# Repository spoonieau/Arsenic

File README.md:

# Smart HVAC Probe

A ESP32-C3 based probe designed for the the automatic matching of r1234yf, r134, HC-30 and R744 refrigerant pressures from current atmospheric temperature.

## Features
This Probe is designed for the the automatic matching of r1234yf, r134, HC-30 and R744 refrigerant pressures from current atmospheric temperature.

It is also equipped with a vent probe for use automotive air conditioning performance testing.

Charged and programmed over USB -C 

The probe is a fully enabled WiFi device hosting its own micro web server to to display sensor and pressure data. Any device with a WiFi connection and a web browser can connect. 

Once booted the probe will broadcast a WiFi Connection with the details below.

SSID: Smart_Hvac_Probe  
Default Password: Smart_Hvac_Probe  
Probes IP: 192.168.4.1  

Once WiFi connection is established between probe and device, a device the web browser should redirect you the the hosted probes home page. If not, type the probes IP address into a connect web browser address bar.
 
Once at the Probes homepage you can change the WiFi details and set the default units to used by the probe.  
When any setting are updated the Probe will reboot and you device will need to reconnect with the new details. 

## Screenshots
PCB_V3_EE  

FireFox Mobile  

FireFox PC  

## Used Libraries
A huge thankyou to the authors of the libraries used below.  

PaulStoffregen - OneWire  
https://github.com/PaulStoffregen/OneWire

milesburton - Arduino-Temperature-Control-Library  
https://github.com/milesburton/Arduino-Temperature-Control-Library

RadioShuttle - WS2812Led  
https://github.com/RadioShuttle/WS2812Led

hideakitai - MAX17048  
https://github.com/hideakitai/MAX17048

malokhvii-eduard - arduino-bme280  
https://github.com/malokhvii-eduard/arduino-bme280

me-no-dev - ESPAsyncWebServer  
https://github.com/me-no-dev/ESPAsyncWebServer

me-no-dev - AsyncTCP  
https://github.com/me-no-dev/AsyncTCP

arduino-libraries   
https://github.com/arduino-libraries

espressif - arduino-esp32  
https://github.com/espressif/arduino-esp32

## License

Libraries that are used carry their own Licenses.  
Project is released under GPL3

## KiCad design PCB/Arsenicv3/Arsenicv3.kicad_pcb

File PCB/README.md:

KiCad PCB design files for Arsenic Smart HAVC Probe   
Current working version V3

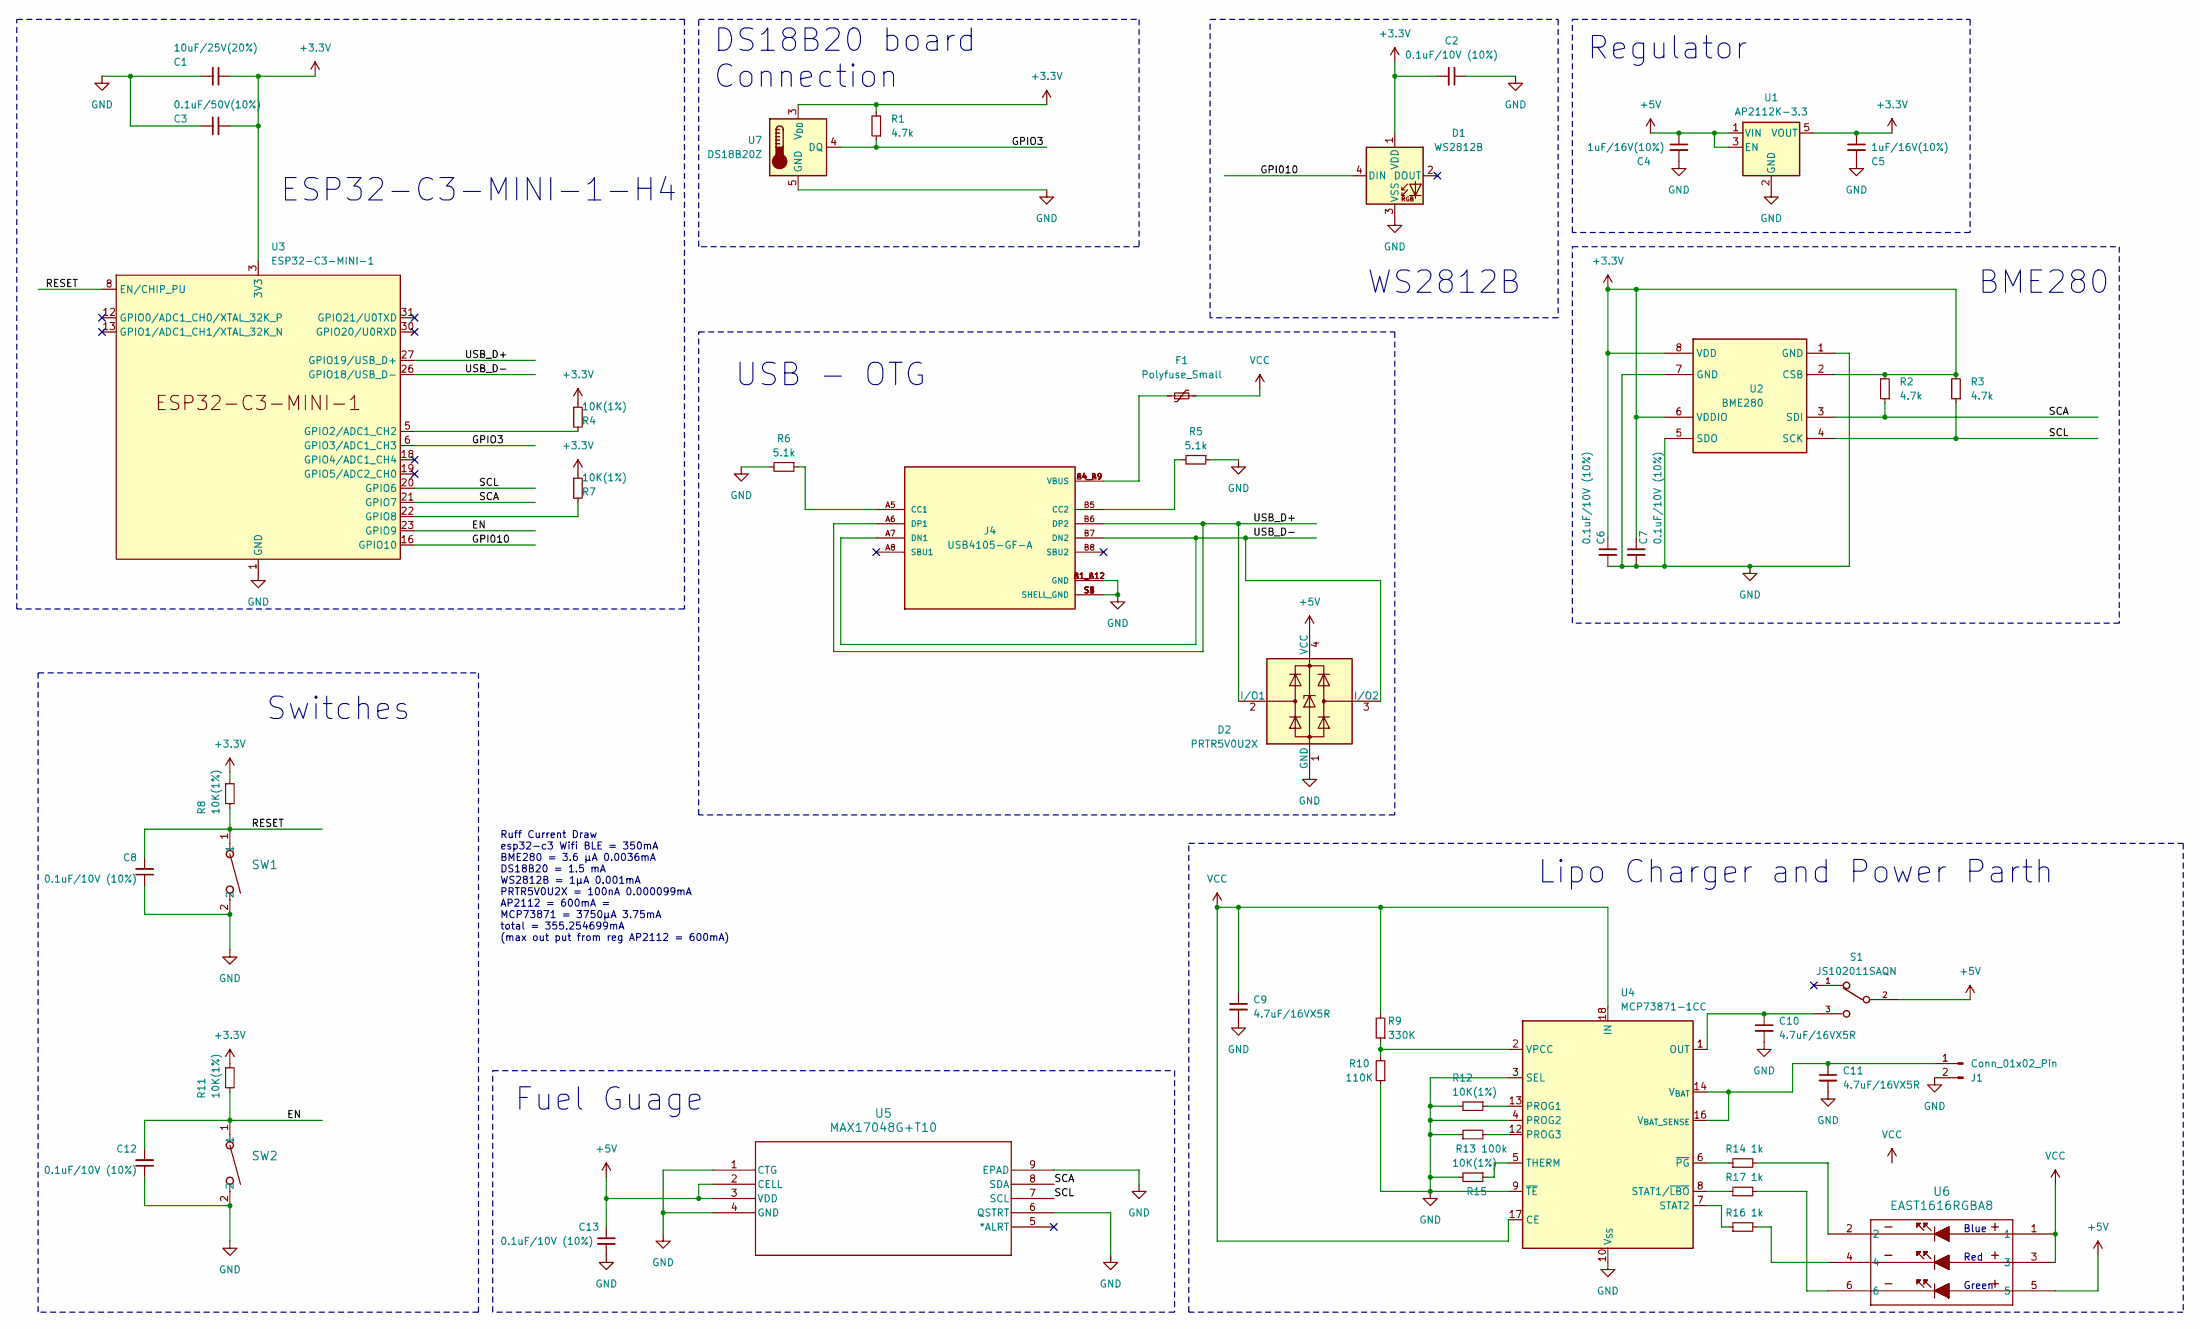
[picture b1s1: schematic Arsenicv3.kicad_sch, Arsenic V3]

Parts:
C1: 10uF/25V(20%); C_0603_1608Metric_Pad1.08x0.95mm_HandSolder; DigiKeyPN 1276-1869-1-ND
C2, C6, C7, C8, C12, C13: 0.1uF/10V (10%); C_0402_1005Metric_Pad0.74x0.62mm_HandSolder; DigiKeyPN 1276-1022-1-ND
C3: 0.1uF/50V(10%); C_0402_1005Metric_Pad0.74x0.62mm_HandSolder; DigiKeyPN 490-GRM155R61H104ME14DCT-ND
C4, C5: 1uF/16V(10%); C_0402_1005Metric_Pad0.74x0.62mm_HandSolder; DigiKeyPN 1276-1067-1-ND
C9, C10, C11: 4.7uF/16VX5R; C_0402_1005Metric_Pad0.74x0.62mm_HandSolder; DigiKeyPN 478-CM05X5R475M16AHCT-ND
D1: WS2812B; LED_WS2812B_PLCC4_5.0x5.0mm_P3.2mm; DigiKeyPN 1568-COM-16347CT-ND
D2: PRTR5V0U2X; SOT-143; DigiKeyPN 1727-3884-1-ND
F1: Polyfuse_Small; Fuse_0805_2012Metric_Pad1.15x1.40mm_HandSolder; DigiKeyPN 13-SMD0805B075TFCT-ND
J1: Conn_01x02_Pin; PinHeader_1x02_P2.00mm_Vertical
J4: USB4105-GF-A; GCT_USB4105-GF-A; DigiKeyPN 2073-USB4105-GF-ACT-ND
R1, R2, R3: 4.7k; R_0402_1005Metric_Pad0.72x0.64mm_HandSolder; DigiKeyPN 311-4.7KLRCT-ND
R4, R7, R8, R11, R12, R15: 10K(1%); C_0402_1005Metric_Pad0.74x0.62mm_HandSolder; DigiKeyPN 311-10.0KLRCT-ND
R5, R6: 5.1k; R_0402_1005Metric_Pad0.72x0.64mm_HandSolder; DigiKeyPN 13-RC0402FR-135K1LCT-ND
R9: 330K; R_0402_1005Metric_Pad0.72x0.64mm_HandSolder; DigiKeyPN 1292-WR04X3303FTLCT-ND
R10: 110K; R_0402_1005Metric_Pad0.72x0.64mm_HandSolder; DigiKeyPN CR0402-FX-1103GLFCT-ND
R13: 100k; R_0402_1005Metric_Pad0.72x0.64mm_HandSolder; DigiKeyPN 311-100KLRCT-ND
R14, R16, R17: 1k; R_0402_1005Metric_Pad0.72x0.64mm_HandSolder; DigiKeyPN 311-1.00KLRCT-ND
S1: JS102011SAQN; SW_JS102011SAQN; DigiKeyPN 401-1999-1-ND
SW1, SW2: KXT331LHS; KXT3_CNK; DigiKeyPN CKN10779CT-ND
U1: AP2112K-3.3; SOT-23-5; DigiKeyPN AP2112K-3.3TRG1DICT-ND
U2: BME280; Bosch_LGA-8_2.5x2.5mm_P0.65mm_ClockwisePinNumbering; DigiKeyPN 828-1063-1-ND
U3: ESP32-C3-MINI-1; DigiKeyPN 1965-ESP32-C3-MINI-1-H4CT-ND
U4: MCP73871-1CC; QFN-20-1EP_4x4mm_P0.5mm_EP2.5x2.5mm; DigiKeyPN MCP73871-1CCI/ML-ND
U5: MAX17048G+T10; 21-0168E_T822-3_MXM; DigiKeyPN MAX17048G+T10CT-ND
U6: EAST1616RGBA8; LED_EAST1616RGBA8; DigiKeyPN 1080-EAST1616RGBA8CT-ND
U7: DS18B20Z; SOIC-8_3.9x4.9mm_P1.27mm; DigiKeyPN 4518-DS18B20ZCT-ND

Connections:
+3.3V: C1.1, C2.2, C3.1, C5.1, C6.1, C7.1, D1.1 (VDD), R1.2, R2.2, R3.2, R4.1, R7.1, R8.1, R11.1, U1.5 (VOUT), U2.2 (CSB), U2.6 (VDDIO), U2.8 (VDD), U3.3 (3V3), U7.3 (V_{DD})
+5V: C4.1, C13.1, D2.4 (VCC), S1.2, U1.1 (VIN), U1.3 (EN), U5.2 (CELL), U5.3 (VDD), U6.5
/EN: C12.2, R11.2, SW2.1, U3.23 (GPIO9)
/GPI010: D1.4 (DIN), U3.16 (GPIO10)
/GPIO3: R1.1, U3.6 (GPIO3/ADC1_CH3), U7.4 (DQ)
/RESET: C8.2, R8.2, SW1.1, U3.8 (EN/CHIP_PU)
/SCA: R2.1, U2.3 (SDI), U3.21 (GPIO7), U5.8 (SDA)
/SCL: R3.1, U2.4 (SCK), U3.20 (GPIO6), U5.7 (SCL)
/USB_D+: D2.2 (I/O1), J4.A6 (DP1), J4.B6 (DP2), U3.27 (GPIO19/USB_D+)
/USB_D-: D2.3 (I/O2), J4.A7 (DN1), J4.B7 (DN2), U3.26 (GPIO18/USB_D-)
GND: C1.2, C2.1, C3.2, C4.2, C5.2, C6.2, C7.2, C8.1, C9.2, C10.2, C11.2, C12.1, C13.2, D1.3 (VSS), D2.1 (GND), J1.2, J4.A1_B12 (GND), J4.B1_A12 (GND), J4.S1 (SHELL_GND), J4.S2 (SHELL_GND), J4.S3 (SHELL_GND), J4.S4 (SHELL_GND), R5.1, R6.2, R10.1, R12.2, R13.1, R15.2, SW1.2, SW2.2, U1.2 (GND), U2.1 (GND), U2.5 (SDO), U2.7 (GND), U3.1 (GND), U3.2 (GND), U3.11 (GND), U3.14 (GND), U3.36 (GND), U3.37 (GND), U3.38 (GND), U3.39 (GND), U3.40 (GND), U3.41 (GND), U3.42 (GND), U3.43 (GND), U3.44 (GND), U3.45 (GND), U3.46 (GND), U3.47 (GND), U3.48 (GND), U3.49 (GND), U3.50 (GND), U3.51 (GND), U3.52 (GND), U3.53 (GND), U4.3 (SEL), U4.4 (PROG2), U4.9 (~TE), U4.10 (V_{SS}), U4.11 (V_{SS}), U4.21 (V_{SS}), U5.1 (CTG), U5.4 (GND), U5.6 (QSTRT), U5.9 (EPAD), U7.5 (GND)
unnamed: C10.1, S1.3, U4.1 (OUT), U4.20 (OUT)
unnamed: F1.1, J4.A4_B9 (VBUS), J4.B4_A9 (VBUS)
unnamed: C11.1, J1.1, U4.14 (V_{BAT}), U4.15 (V_{BAT}), U4.16 (V_{BAT_SENSE})
unnamed: J4.A5 (CC1), R6.1
unnamed: J4.B5 (CC2), R5.2
unnamed: R14.2, U6.2
unnamed: R16.2, U6.4
unnamed: R17.2, U6.6
unnamed: R4.2, U3.5 (GPIO2/ADC1_CH2)
unnamed: R7.2, U3.22 (GPIO8)
unnamed: R12.1, U4.13 (PROG1)
unnamed: R13.2, U4.12 (PROG3)
unnamed: R17.1, U4.8 (STAT1/~LBO)
unnamed: R16.1, U4.7 (STAT2)
unnamed: R15.1, U4.5 (THERM)
unnamed: R9.1, R10.2, U4.2 (VPCC)
unnamed: R14.1, U4.6 (~PG)
VCC: C9.1, F1.2, R9.2, U4.17 (CE), U4.18 (IN), U4.19 (IN), U6.1, U6.3

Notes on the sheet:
WS2812B
Regulator
Fuel Guage
Lipo Charger and Power Parth
Green
USB - OTG
ESP32-C3-MINI-1-H4
BME280
Switches
Red
Blue
Ruff Current Draw esp32-c3 Wifi BLE = 350mA BME280 = 3.6 μA 0.0036mA DS18B20 = 1.5 mA WS2812B = 1μA 0.001mA PRTR5V0U2X = 100nA 0.000099mA AP2112 = 600mA = MCP73871 = 3750μA 3.75mA total = 355.254699mA (max out put from reg AP2112 = 600mA)
DS18B20 board Connection

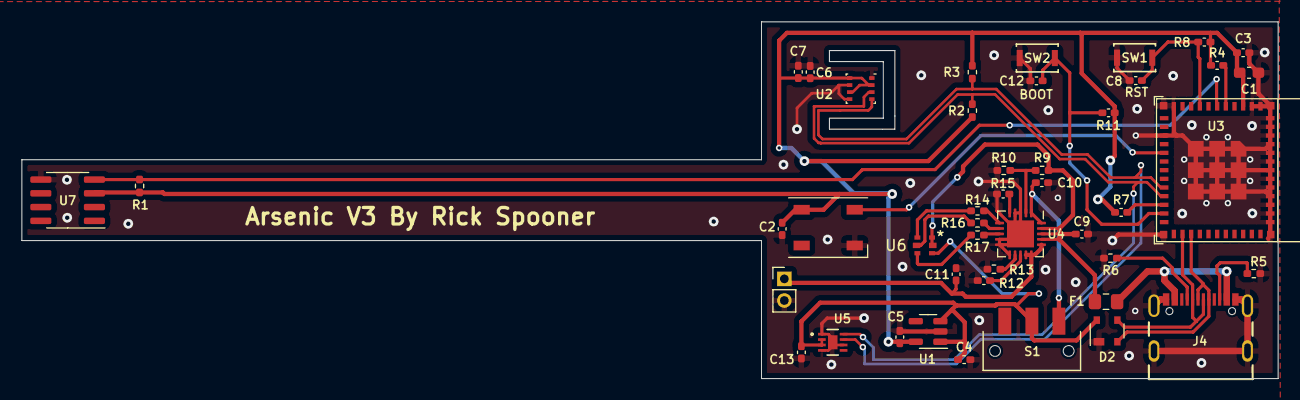
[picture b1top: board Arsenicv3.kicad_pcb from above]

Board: 2 copper layers, 116.0 x 33.0 mm, 45 parts (0 on the bottom side), 29 nets.

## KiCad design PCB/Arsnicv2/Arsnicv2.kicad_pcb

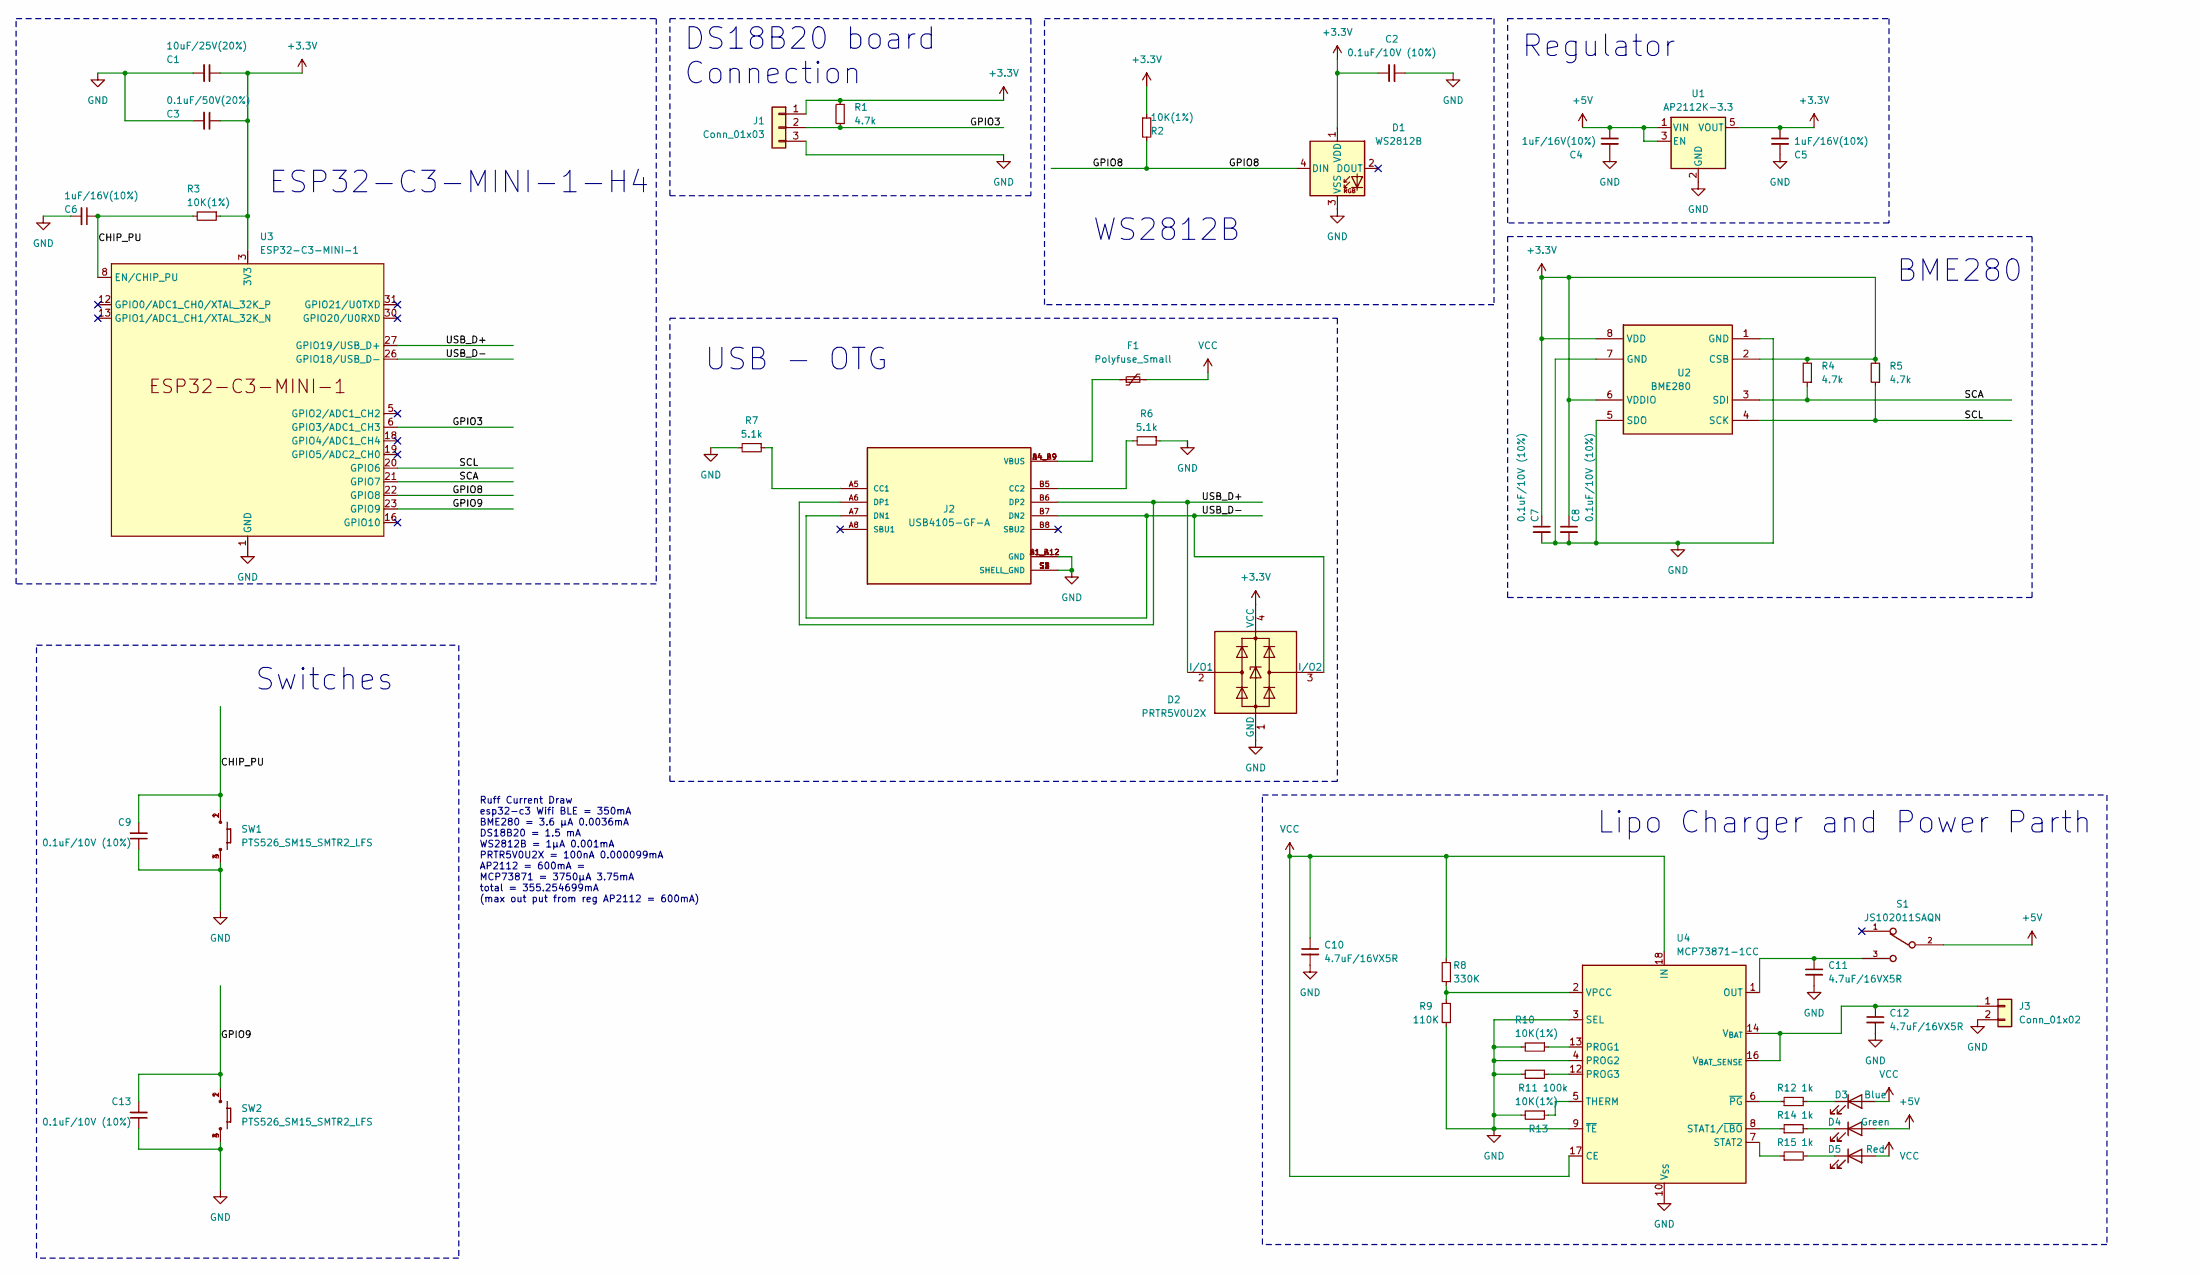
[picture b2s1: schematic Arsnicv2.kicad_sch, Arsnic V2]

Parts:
C1: 10uF/25V(20%); C_0603_1608Metric_Pad1.08x0.95mm_HandSolder; DigiKeyPN 1276-1869-1-ND
C2, C7, C8, C9, C13: 0.1uF/10V (10%); C_0402_1005Metric_Pad0.74x0.62mm_HandSolder; DigiKeyPN 1276-1022-1-ND
C3: 0.1uF/50V(20%); C_0402_1005Metric_Pad0.74x0.62mm_HandSolder; DigiKeyPN 490-GRM155R61H104ME14DCT-ND
C4, C5, C6: 1uF/16V(10%); C_0402_1005Metric_Pad0.74x0.62mm_HandSolder; DigiKeyPN 1276-1067-1-ND
C10, C11, C12: 4.7uF/16VX5R; C_0402_1005Metric_Pad0.74x0.62mm_HandSolder; DigiKeyPN 478-CM05X5R475M16AHCT-ND
D1: WS2812B; LED_WS2812B_PLCC4_5.0x5.0mm_P3.2mm; DigiKeyPN 1568-COM-16347CT-ND
D2: PRTR5V0U2X; SOT-143; DigiKeyPN 1727-3884-1-ND
D3: Blue; LED_0201_0603Metric_Pad0.64x0.40mm_HandSolder; DigiKeyPN 1830-1068-1-ND
D4: Green; LED_0201_0603Metric_Pad0.64x0.40mm_HandSolder; DigiKeyPN 1830-1069-1-ND
D5: Red; LED_0201_0603Metric_Pad0.64x0.40mm_HandSolder; DigiKeyPN 1830-1072-1-ND
F1: Polyfuse_Small; Fuse_0805_2012Metric_Pad1.15x1.40mm_HandSolder; DigiKeyPN 13-SMD0805B075TFCT-ND
J1: Conn_01x03; JST_PH_S3B-PH-K_1x03_P2.00mm_Horizontal; DigiKeyPN S3B-PH-K-S-GW-ND
J2: USB4105-GF-A; GCT_USB4105-GF-A; DigiKeyPN 2073-USB4105-GF-ACT-ND
J3: Conn_01x02; JST_PH_S2B-PH-K_1x02_P2.00mm_Horizontal; DigiKeyPN 455-1719-ND
R1, R4, R5: 4.7k; R_0402_1005Metric_Pad0.72x0.64mm_HandSolder; DigiKeyPN 311-4.7KLRCT-ND
R2, R3, R10, R13: 10K(1%); C_0402_1005Metric_Pad0.74x0.62mm_HandSolder; DigiKeyPN 311-10.0KLRCT-ND
R6, R7: 5.1k; R_0402_1005Metric_Pad0.72x0.64mm_HandSolder; DigiKeyPN 13-RC0402FR-135K1LCT-ND
R8: 330K; R_0402_1005Metric_Pad0.72x0.64mm_HandSolder; DigiKeyPN 1292-WR04X3303FTLCT-ND
R9: 110K; R_0402_1005Metric_Pad0.72x0.64mm_HandSolder; DigiKeyPN CR0402-FX-1103GLFCT-ND
R11: 100k; R_0402_1005Metric_Pad0.72x0.64mm_HandSolder; DigiKeyPN 311-100KLRCT-ND
R12, R14, R15: 1k; R_0402_1005Metric_Pad0.72x0.64mm_HandSolder; DigiKeyPN 311-1.00KLRCT-ND
S1: JS102011SAQN; SW_JS102011SAQN; DigiKeyPN 401-1999-1-ND
SW1, SW2: PTS526_SM15_SMTR2_LFS; PTS526SM15SMTR2LFS; DigiKeyPN CKN12220-1-ND
U1: AP2112K-3.3; SOT-23-5; DigiKeyPN AP2112K-3.3TRG1DICT-ND
U2: BME280; Bosch_LGA-8_2.5x2.5mm_P0.65mm_ClockwisePinNumbering; DigiKeyPN 828-1063-1-ND
U3: ESP32-C3-MINI-1; ESP32-C3-MINI-1_HandSoldering; DigiKeyPN 1965-ESP32-C3-MINI-1-H4CT-ND
U4: MCP73871-1CC; QFN-20-1EP_4x4mm_P0.5mm_EP2.5x2.5mm; DigiKeyPN MCP73871-1CCI/ML-ND

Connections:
+3.3V: C1.1, C2.2, C3.1, C5.1, C7.1, C8.1, D1.1 (VDD), D2.4 (VCC), J1.1, R1.2, R2.1, R3.1, R4.2, R5.2, U1.5 (VOUT), U2.2 (CSB), U2.6 (VDDIO), U2.8 (VDD), U3.3 (3V3)
+5V: C4.1, D4.2 (A), S1.2, U1.1 (VIN), U1.3 (EN)
/CHIP_PU: C6.1, C9.2, R3.2, SW1.1, SW1.2, U3.8 (EN/CHIP_PU)
/GPIO3: J1.2, R1.1, U3.6 (GPIO3/ADC1_CH3)
/GPIO8: D1.4 (DIN), R2.2, U3.22 (GPIO8)
/GPIO9: C13.2, SW2.1, SW2.2, U3.23 (GPIO9)
/SCA: R4.1, U2.3 (SDI), U3.21 (GPIO7)
/SCL: R5.1, U2.4 (SCK), U3.20 (GPIO6)
/USB_D+: D2.2 (I/O1), J2.A6 (DP1), J2.B6 (DP2), U3.27 (GPIO19/USB_D+)
/USB_D-: D2.3 (I/O2), J2.A7 (DN1), J2.B7 (DN2), U3.26 (GPIO18/USB_D-)
GND: C1.2, C2.1, C3.2, C4.2, C5.2, C6.2, C7.2, C8.2, C9.1, C10.2, C11.2, C12.2, C13.1, D1.3 (VSS), D2.1 (GND), J1.3, J2.A1_B12 (GND), J2.B1_A12 (GND), J2.S1 (SHELL_GND), J2.S2 (SHELL_GND), J2.S3 (SHELL_GND), J2.S4 (SHELL_GND), J3.2, R6.1, R7.2, R9.1, R10.2, R11.1, R13.2, SW1.3, SW1.4, SW2.3, SW2.4, U1.2 (GND), U2.1 (GND), U2.5 (SDO), U2.7 (GND), U3.1 (GND), U3.2 (GND), U3.11 (GND), U3.14 (GND), U3.36 (GND), U3.37 (GND), U3.38 (GND), U3.39 (GND), U3.40 (GND), U3.41 (GND), U3.42 (GND), U3.43 (GND), U3.44 (GND), U3.45 (GND), U3.46 (GND), U3.47 (GND), U3.48 (GND), U3.49 (GND), U3.50 (GND), U3.51 (GND), U3.52 (GND), U3.53 (GND), U4.3 (SEL), U4.4 (PROG2), U4.9 (~TE), U4.10 (V_{SS}), U4.11 (V_{SS}), U4.21 (V_{SS})
unnamed: C11.1, S1.3, U4.1 (OUT), U4.20 (OUT)
unnamed: D3.1 (K), R12.2
unnamed: D4.1 (K), R14.2
unnamed: D5.1 (K), R15.2
unnamed: F1.1, J2.A4_B9 (VBUS), J2.B4_A9 (VBUS)
unnamed: J2.A5 (CC1), R7.1
unnamed: J2.B5 (CC2), R6.2
unnamed: C12.1, J3.1, U4.14 (V_{BAT}), U4.15 (V_{BAT}), U4.16 (V_{BAT_SENSE})
unnamed: R10.1, U4.13 (PROG1)
unnamed: R11.2, U4.12 (PROG3)
unnamed: R14.1, U4.8 (STAT1/~LBO)
unnamed: R15.1, U4.7 (STAT2)
unnamed: R13.1, U4.5 (THERM)
unnamed: R8.1, R9.2, U4.2 (VPCC)
unnamed: R12.1, U4.6 (~PG)
VCC: C10.1, D3.2 (A), D5.2 (A), F1.2, R8.2, U4.17 (CE), U4.18 (IN), U4.19 (IN)

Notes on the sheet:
WS2812B
Regulator
Lipo Charger and Power Parth
USB - OTG
ESP32-C3-MINI-1-H4
BME280
Switches
Ruff Current Draw esp32-c3 Wifi BLE = 350mA BME280 = 3.6 μA 0.0036mA DS18B20 = 1.5 mA WS2812B = 1μA 0.001mA PRTR5V0U2X = 100nA 0.000099mA AP2112 = 600mA = MCP73871 = 3750μA 3.75mA total = 355.254699mA (max out put from reg AP2112 = 600mA)
DS18B20 board Connection

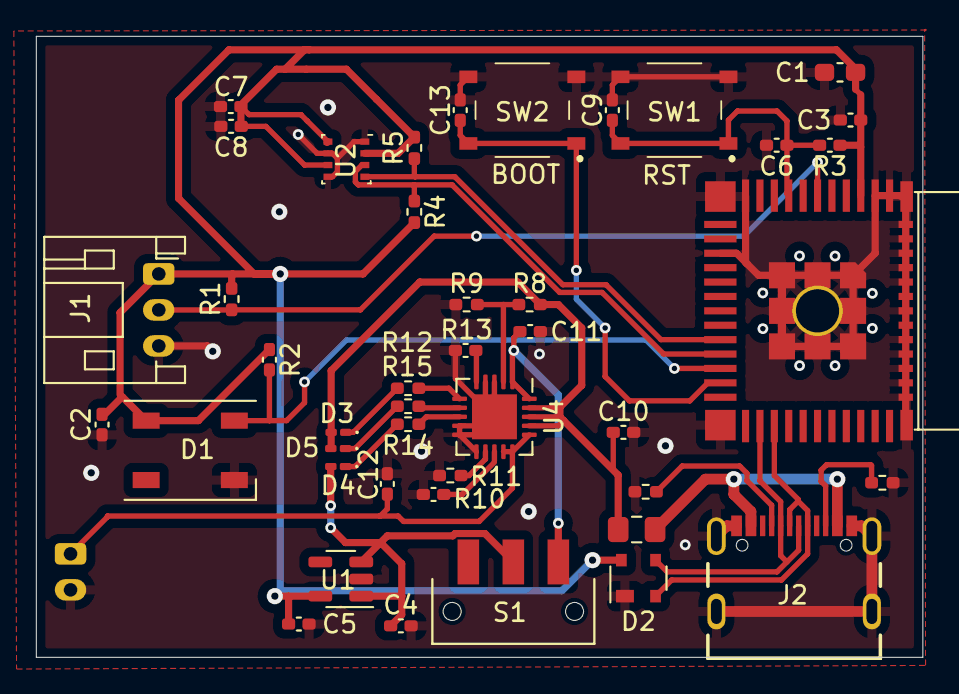
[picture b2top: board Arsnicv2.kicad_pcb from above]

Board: 2 copper layers, 49.3 x 34.5 mm, 44 parts (1 on the bottom side), 27 nets.

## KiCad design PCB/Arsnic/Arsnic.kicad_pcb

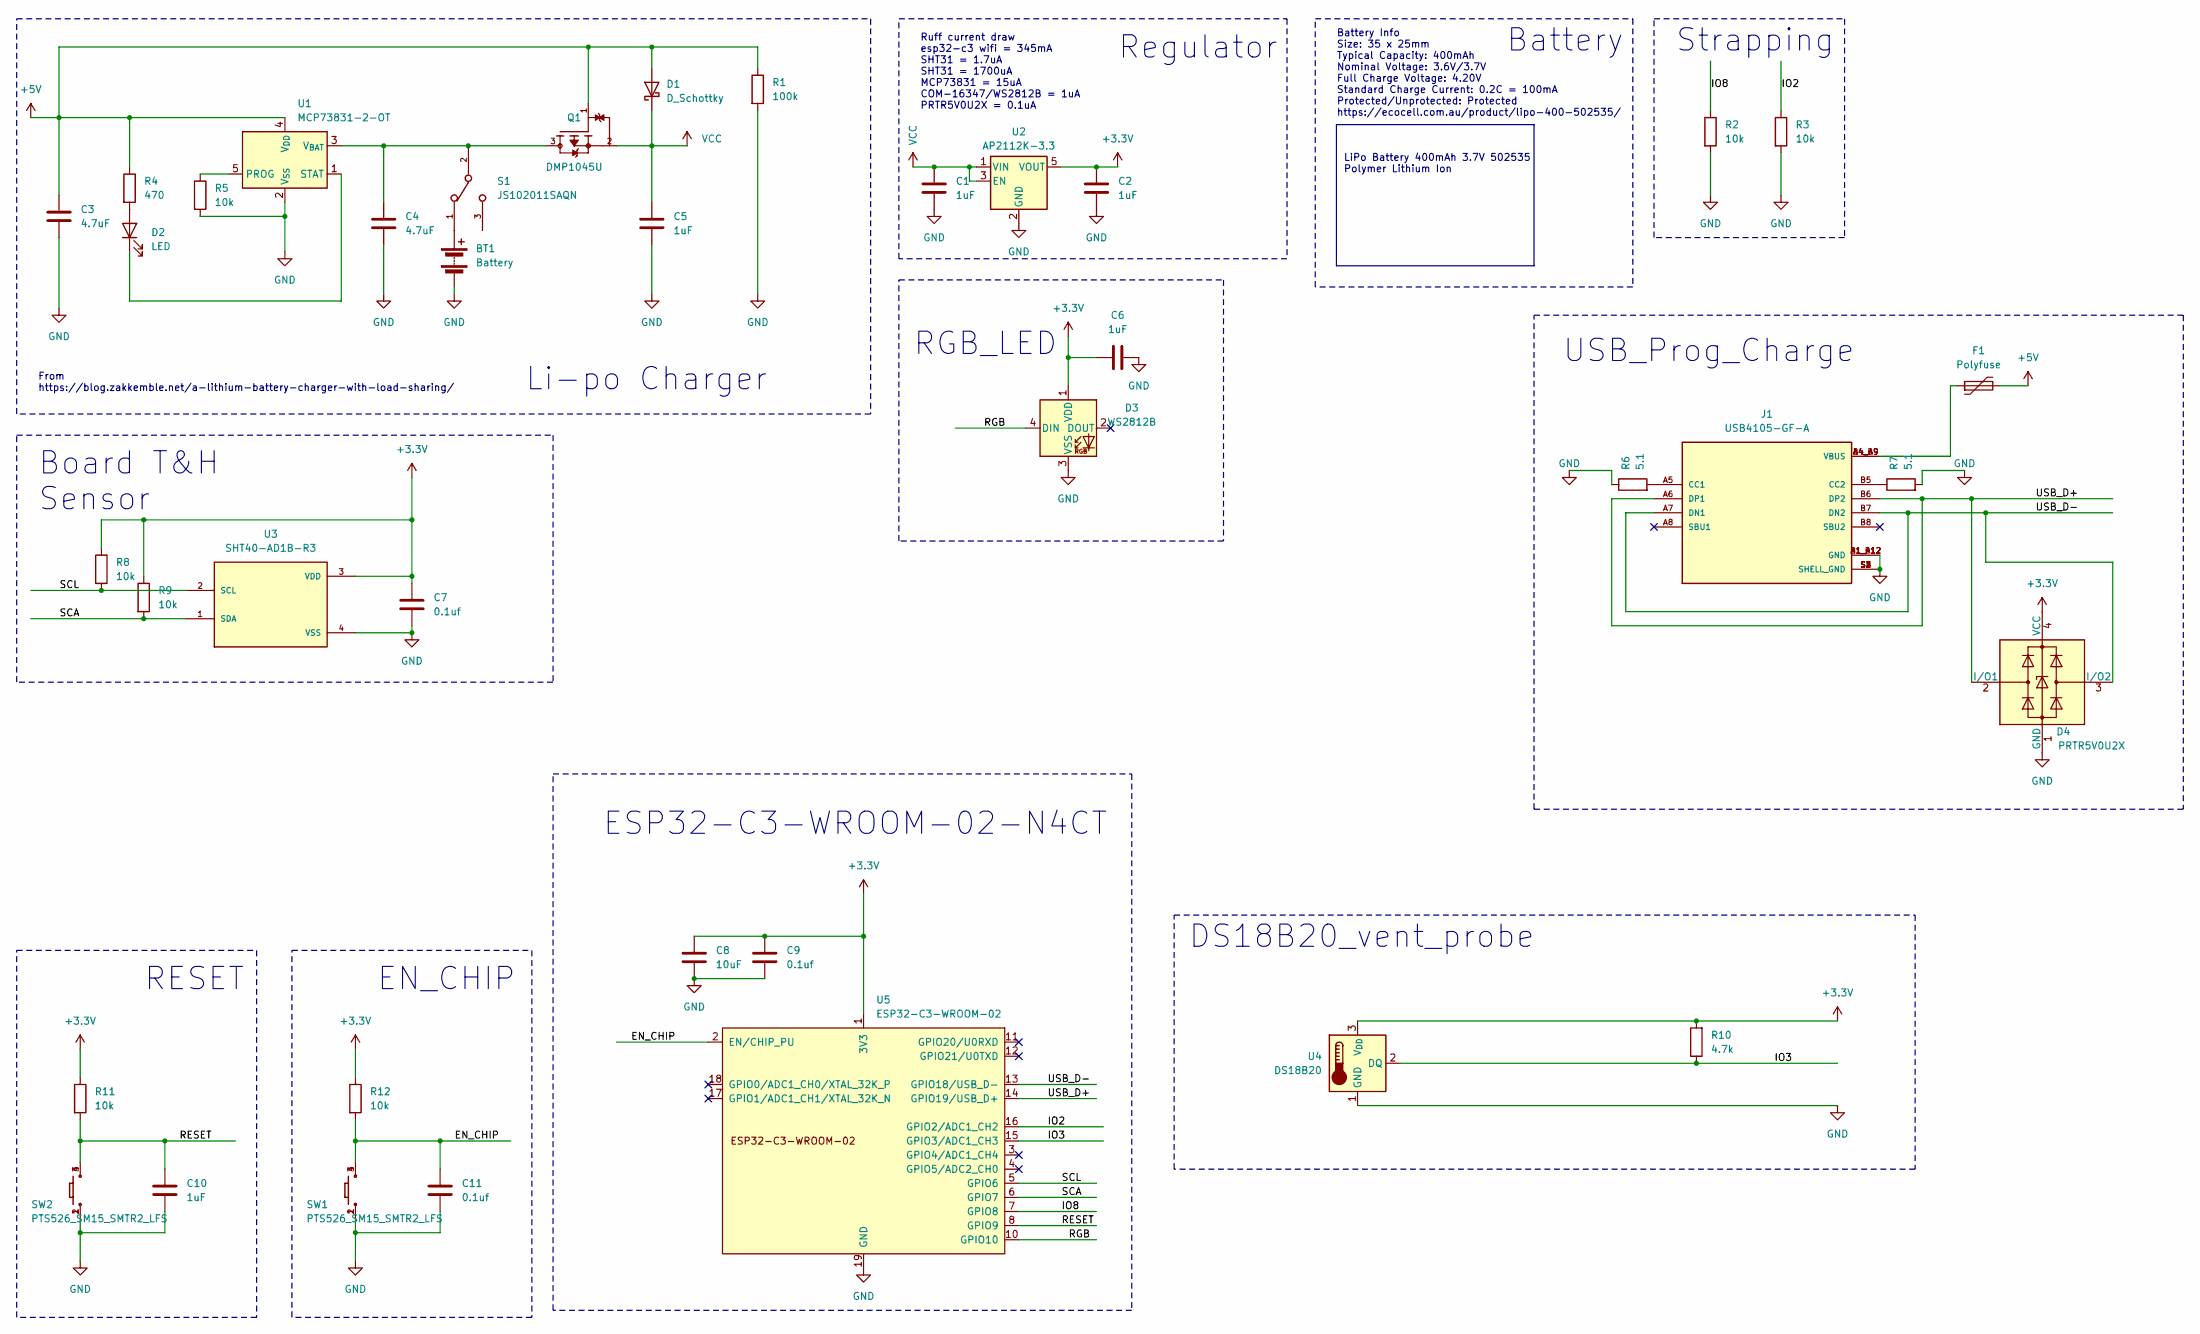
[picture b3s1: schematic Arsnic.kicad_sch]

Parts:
BT1: Battery; LED_D2.0mm_W4.8mm_H2.5mm_FlatTop; PartNumber LIPO-400-502535
C1, C2, C5, C6, C10: 1uF; C_0402_1005Metric_Pad0.74x0.62mm_HandSolder; DigiKeyPN 1276-1076-1-ND - Cut Tape (CT)
C3, C4: 4.7uF; C_0402_1005Metric_Pad0.74x0.62mm_HandSolder; DigiKeyPN 1276-1481-1-ND - Cut Tape (CT)
C7, C9, C11: 0.1uf; C_0402_1005Metric_Pad0.74x0.62mm_HandSolder; DigiKeyPN 478-11504-1-ND - Cut Tape (CT)
C8: 10uF; C_0603_1608Metric_Pad1.08x0.95mm_HandSolder; DigiKeyPN 1276-1119-1-ND - Cut Tape
D1: D_Schottky; D_SOD-123; DigiKeyPN B130LAW-FDICT-ND - Cut Tape (CT)
D2: LED; LED_Rectangular_W3.0mm_H2.0mm; DigiKeyPN 754-1901-ND
D3: WS2812B; LED_WS2812B_PLCC4_5.0x5.0mm_P3.2mm; DigiKeyPN 1568-COM-16347CT-ND - Cut Tape (CT)
D4: PRTR5V0U2X; SOT-143; DigiKeyPN 1727-3884-1-ND - Cut Tape (CT)
F1: Polyfuse; Fuse_1206_3216Metric_Pad1.42x1.75mm_HandSolder; DigiKeyPN F2112CT-ND - Cut Tape (CT)
J1: USB4105-GF-A; GCT_USB4105-GF-A; DigiKeyPN 2073-USB4105-GF-ACT-ND - Cut Tape (CT)
Q1: DMP1045U; SOT91P240X110-3N; DigiKeyPN DMP1045U-7DICT-ND - Cut Tape (CT)
R1: 100k; R_0402_1005Metric_Pad0.72x0.64mm_HandSolder; DigiKeyPN 1292-WR04X104JTLCT-ND - Cut Tape (CT)
R2, R3, R5, R8, R9, R11, R12: 10k; C_0402_1005Metric_Pad0.74x0.62mm_HandSolder; DigiKeyPN 311-10.0KLRCT-ND - Cut Tape (CT)
R4: 470; R_0402_1005Metric_Pad0.72x0.64mm_HandSolder; DigiKeyPN 1292-WR04X4700FTLCT-ND - Cut Tape (CT)
R6, R7: 5.1; C_0402_1005Metric_Pad0.74x0.62mm_HandSolder; DigiKeyPN 311-5.1JRCT-ND - Cut Tape (CT)
R10: 4.7k; R_0402_1005Metric_Pad0.72x0.64mm_HandSolder; DigiKeyPN 311-4.7KLRCT-ND - Cut Tape (CT)
S1: JS102011SAQN; SW_JS102011SAQN; DigiKeyPN 401-1999-1-ND - Cut Tape (CT)
SW1, SW2: PTS526_SM15_SMTR2_LFS; PTS526SM15SMTR2LFS; DigiKeyPN CKN12220-1-ND - Cut Tape (CT)
U1: MCP73831-2-OT; SOT-23-5; DigiKeyPN MCP73831T-2ACI/OTCT-ND - Cut Tape (CT)
U2: AP2112K-3.3; SOT-23-5; DigiKeyPN AP2112K-3.3TRG1DICT-ND - Cut Tape (CT)
U3: SHT40-AD1B-R3; SHT4X; DigiKeyPN 1649-SHT40-AD1B-R3CT-ND
U4: DS18B20; TO-92_Inline; DigiKeyPN 1528-1592-ND
U5: ESP32-C3-WROOM-02; DigiKeyPN 1965-ESP32-C3-WROOM-02-N4CT-ND

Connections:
+3.3V: C2.1, C6.1, C7.1, C8.1, C9.1, D3.1 (VDD), D4.4 (VCC), R8.1, R9.1, R10.2, R11.1, R12.1, U2.5 (VOUT), U3.3 (VDD), U4.3 (V_{DD}), U5.1 (3V3)
+5V: C3.1, D1.2 (A), F1.2, Q1.1, R1.1, R4.1, U1.4 (V_{DD})
/EN_CHIP: C11.1, R12.2, SW1.3, SW1.4, U5.2 (EN/CHIP_PU)
/IO2: R3.1, U5.16 (GPIO2/ADC1_CH2)
/IO3: R10.1, U4.2 (DQ), U5.15 (GPIO3/ADC1_CH3)
/IO8: R2.1, U5.7 (GPIO8)
/RESET: C10.1, R11.2, SW2.3, SW2.4, U5.8 (GPIO9)
/RGB: D3.4 (DIN), U5.10 (GPIO10)
/SCA: R9.2, U3.1 (SDA), U5.6 (GPIO7)
/SCL: R8.2, U3.2 (SCL), U5.5 (GPIO6)
/USB_D+: D4.2 (I/O1), J1.A6 (DP1), J1.B6 (DP2), U5.14 (GPIO19/USB_D+)
/USB_D-: D4.3 (I/O2), J1.A7 (DN1), J1.B7 (DN2), U5.13 (GPIO18/USB_D-)
GND: BT1.2 (-), C1.2, C2.2, C3.2, C4.2, C5.2, C6.2, C7.2, C8.2, C9.2, C10.2, C11.2, D3.3 (VSS), D4.1 (GND), J1.A1_B12 (GND), J1.B1_A12 (GND), J1.S1 (SHELL_GND), J1.S2 (SHELL_GND), J1.S3 (SHELL_GND), J1.S4 (SHELL_GND), R1.2, R2.2, R3.2, R5.2, R6.1, R7.2, SW1.1, SW1.2, SW2.1, SW2.2, U1.2 (V_{SS}), U2.2 (GND), U3.4 (VSS), U4.1 (GND), U5.9 (GND), U5.19 (GND)
unnamed: BT1.1 (+), S1.1
unnamed: D2.2 (A), R4.2
unnamed: D2.1 (K), U1.1 (STAT)
unnamed: F1.1, J1.A4_B9 (VBUS), J1.B4_A9 (VBUS)
unnamed: J1.A5 (CC1), R6.2
unnamed: J1.B5 (CC2), R7.1
unnamed: R5.1, U1.5 (PROG)
unnamed: C4.1, Q1.3, S1.2, U1.3 (V_{BAT})
VCC: C1.1, C5.1, D1.1 (K), Q1.2, U2.1 (VIN), U2.3 (EN)

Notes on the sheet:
Battery
RESET
USB_Prog_Charge
Li-po Charger
EN_CHIP
Board T&H Sensor
ESP32-C3-WROOM-02-N4CT
Regulator
Ruff current draw esp32-c3 wifi = 345mA SHT31 = 1.7uA SHT31 = 1700uA MCP73831 = 15uA COM-16347/WS2812B = 1uA PRTR5V0U2X = 0.1uA
Battery Info Size: 35 x 25mm Typical Capacity: 400mAh Nominal Voltage: 3.6V/3.7V Full Charge Voltage: 4.20V Standard Charge Current: 0.2C = 100mA Protected/Unprotected: Protected https://ecocell.com.au/product/lipo-400-502535/
Strapping
DS18B20_vent_probe
From https://blog.zakkemble.net/a-lithium-battery-charger-with-load-sharing/
RGB_LED
LiPo Battery 400mAh 3.7V 502535 Polymer Lithium Ion

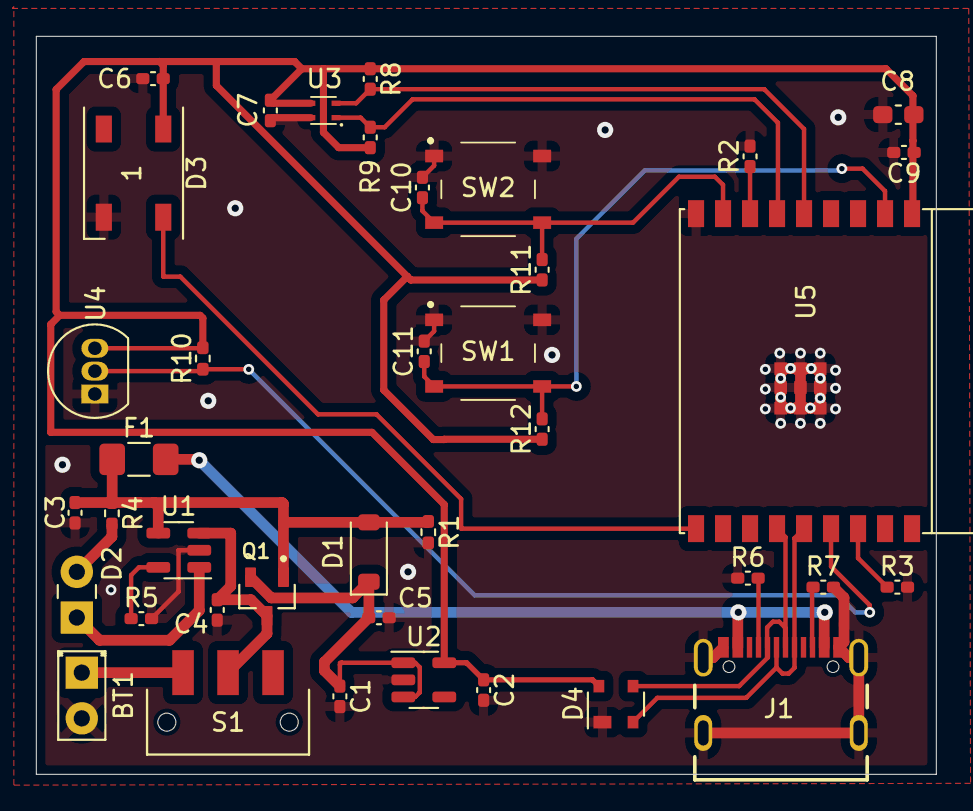
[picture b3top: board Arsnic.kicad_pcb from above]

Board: 2 copper layers, 50.0 x 41.0 mm, 39 parts (0 on the bottom side), 22 nets.

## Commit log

2024-03-07 Initial Release
2024-03-07 Update README.md
    spelling
